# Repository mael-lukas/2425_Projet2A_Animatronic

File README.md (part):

<h1 align="center"> DEA : Dynamic Eagle Animatronic</h1>

<p align="center">An english version of this README file can be found below the french one</p>

<h2 align="center">Préambule</h2>
Depuis la Grêce antique et le mythe du géant de bronze Talos, les hommes ont toujours cherchés à créer des automates avec les moyens à leur disposition. Les animatroniques sont l'achèvement actuel de ce désir. Ce sont des poupées mécaniques plus ou moins réalistes dont le fonctionnement interne fait intervenir autant la mécanique que l'électronique.
Elles sont, depuis plusieurs décennies, et encore aujourd'hui principalement utilisées dans le domaine du divertissement au travers des parcs d'attractions, des films et des séries.

Dans le cadre d'un projet de deuxième année à l'école d'ingénieur française ENSEA ( École Nationale Supérieure de l'Électronique et de ses Applications), nous allons continuer la création d'une animatronique d'aigle royal démarrée au second semestre de l'année dernière.

# Sommaire 
  * #### Équipe et détail des tâches
  * #### Électronique et CAO
  * #### Modélisation & Impression 3D
  * #### Mécanique
  * #### Informatique
  * #### Résultat final
  * #### Points d'amélioration
  * #### Conclusion

<table>
  <tr>
    <td></td>
    <td></td>
  </tr>
</table>

<h1 align="center">Équipe</h1>

Membres de l'équipe : 
* #### Vincent Fernandes
    * [Github](https://github.com/FernandesVincent)
    * [Linkedin](https://www.linkedin.com/in/vincent-fernandes-0981552a6/)
* #### Maël Lukas
    * [Github](https://github.com/mael-lukas)
    * [Linkedin](https://www.linkedin.com/in/mael-lukas/)
* ##### Romane Ponthieu
    * [Github](https://github.com/Romanepnth)
    * [Linkedin](https://www.linkedin.com/in/romane-ponthieu/)
* #### Sedrenn Labrousse
    * [Github](https://github.com/Sedrennl)
    * [Linkedin](https://www.linkedin.com/in/sédrenn-labrousse-24b2a5295/)

* #### Supervisé par Nicolas Papazoglou
    * [Github](https://github.com/DBXYD?tab=overview&from=2024-05-01&to=2024-05-29)
    * [Linkedin](https://www.linkedin.com/in/nicolas-papazoglou-38382646/?originalSubdomain=fr)
 
* #### Supervisé par Laurent Fiack
    * [Github](https://github.com/lfiack)
    * [Linkedin](https://fr.linkedin.com/in/laurent-fiack-1b1415124)

Nous vous invitons à consulter notre [github de l'année dernière](https://github.com/mael-lukas/2324_Projet1AB_Animatronic), dans lequel vous pourrez trouver toutes les bases sur lesquelles nous avons démarré ce projet.

Ce projet s'articule autour de plusieurs compétences techniques : informatique, électronique & CAO, modélisation & impression 3D et mécanique. Chacune ayant partagée entre différents membres de l'équipe.

   * Informatique

Cette partie a été majoritairement traitée par Maël avec également, de manière plus minoritaire, Vincent.
Dans cette partie nous allons voir comment tout le code nécessaire au bon fonctionnement du DEA se présente. En partant de simple envoies de PWM pour commander des servomoteurs à la programmation de moteurs plus complexes, en passant par l'allumage de LED neopxiel et de la communication Bluetooth.

   * Électronique & CAO

Cette partie concerne différentes sous compétences : la conception des PCB, la soudure de ceux-ci, les test associés et finalement le sertissage et cablâge. 
Comme notre projet inclus plusieurs PCBs, leur conception a été réalisée par Vincent (pour les PCBs du corps et du gant) et Romane (pour le PCB de la tête).
Les soudures CMS ont été réalisées par Maël et Romane, tandis que les soudures THT ont été effectuées par Vincent.
Le sertissage et le cablâge ont également été réalisé par Vincent.

   * Modélisation & Impression 3D

Cette partie a été essentiellement traitée par Sedrenn aidée de Romane et Vincent. L'objectif de celle-ci étant de modéliser et d'imprimer l'aigle en taille 1:1 ainsi que des caches pour protéger l'alimentation et les PCBs.

   * Mécanique

Cette partie concerne la gestion des différents moteurs qui a été faite par Maël pour l'implémentation du code, par Vincent pour le cablâge de ceux-ci et leur placement sur la structure de l'aigle mais également par Sedrenn et Romane pour la conception des pièces 3D permettant de faire les liaisons entre ceux-ci.

<h1 align="center">Électronique & CAO</h1>

Pour commencer, veuillez trouver ci-dessous le diagramme d'architecture qui nous a servis de base pour la création des PCB de ce projet:

<div align="center">
  
</div>

Voici donc, le schematic et le routage du PCB principal de projet, le PCB du corps :

<table>
  <tr>
    <td></td>
    <td></td>
  </tr>
</table>

Ce PCB a eu le droit à plusieurs versions afin de l'améliorer à chaque ittération. La dernière en date est l'ajout de R1, une résistance de pull-up pour le protocol UART qui nous sert à commander les moteurs. Cependant, une fois ce nouveau PCB soudé et testé nous n'arrivions plus à communiquer avec les moteurs donc nous sommes repassé sur la version antérieure du PCB, qui elle est foncitonnel, où la résistance de pull-up est activée sur STM32CubeIDE.
Vous pouvez trouvez [ici](https://github.com/mael-lukas/2425_Projet2A_Animatronic/blob/main/Hardware/pcb/Body/ProjetCorps.csv)la BOM de ce PCB.

Le second PCB que nous avons du réalisé est celui de la tête, vous constaterez qu'il n'a pas changé depuis [l'année dernière](https://github.com/mael-lukas/2324_Projet1AB_Animatronic) voici donc simplement son schematic, son routage et sa BOM :

<table>
  <tr>
    <td></td>
    <td></td>
  </tr>
</table>

[BOM](https://github.com/mael-lukas/2425_Projet2A_Animatronic/blob/main/Hardware/pcb/Head/bom%20t%C3%AAte)

Il est à noter qu'avec plus de temps nous aurions suremenent modifier ce PCB car les besoins de notre projet ont changés, nous n'avons plus besoin de contrôler six servomoteurs mais par contre nous avons besoin d'une piste GPIO pour contrôler l'état haut ou bas de la pin XSDN du [TOF](https://github.com/mael-lukas/2425_Projet2A_Animatronic/blob/main/Datasheets/vl53l1x-satel.pdf).

Le troisième et dernier PCB de projet est le PCB du gant qui se présente comme suit :

<table>
  <tr>
    <td></td>
    <td></td>
  </tr>
</table>

[BOM](https://github.com/mael-lukas/2425_Projet2A_Animatronic/blob/main/Hardware/pcb/Gant/PCB_Gant/PCB_Gant.csv)

L'objectif avec ce PCB est de pouvoir commander les mouvements de l'aigle avec les mouvements de nos doigts et ce sans liaison filaire mais avec une liaison bluetooth grâce au module [HC05](https://github.com/mael-lukas/2425_Projet2A_Animatronic/blob/main/Datasheets/HC-05%20Datasheet.pdf). Les empreintes de résistances en 1206 correspondent aux pads des [flex sensors](https://github.com/mael-lukas/2425_Projet2A_Animatronic/blob/main/Datasheets/Flex_Sensor_Datasheet_v2019a-3304101.pdf) qui sont des résistances variables qui nous permmettent grâce aux circuits visibles sur le schematic d'avoir une tension seuil à partir de laquelle on peut activer tel ou tel mouvement de l'aigle.
Pour pouvoir fonctionner via une liaison Bluetooth nous alimentons le PCB grâce à une batterie Li-ion 1S et grâce à un module servant de Boost pour pouvoir amener une tension de +5V au pcb.

Ce PCB pourrait avoir des versions plus évoluées notamment vis à vis des circuits des [flex sensors](https://github.com/mael-lukas/2425_Projet2A_Animatronic/blob/main/Datasheets/Flex_Sensor_Datasheet_v2019a-3304101.pdf) qui peuvent être largement améliorer afin de par exemple pouvoir changer la tension seuil désirée avec des potentiomètres à la place des résistances.

Ce PCB permet également le contrôle du volume du haut parleur grâce à l'encodeur rotatif présent dessus. Pour revenir rapidement sur cette partie "haut parleur", l'objectif est de pouvoir jouer des sons grâce à un haut parleur présents entre les pattes de l'aigle en fonction de la distance avec la personne en face de lui grâce au [TOF](https://github.com/mael-lukas/2425_Projet2A_Animatronic/blob/main/Datasheets/vl53l1x-satel.pdf).Par exemple, si je me trouve à un mètre de l'oiseau il me dira "Bonjour" par contre si je m'approche à dix centimètres de celui-ci il me dira "Recule".

Pour finir cette partie, vous pouvez voir ci-dessous quelques photos des PCB réaliés. Vous constaterez qu'ils sont chacun entourés d'un support fait en impression 3D. Ces supports ne sont pas nécessaire in fine mais ils permettent d'éviter les risques en empéchant les collisions malheureuses entre les PCB, ce qui pourrait amener des problèmes si cela se passe lorsqu'ils sont en fonctionnement.

<h1 align="center">Modélisation & Impression 3D</h1>

Maintenant que nous avons commencé à parler de modélisation 3D il est temps d'attaquer totalement cette partie. En effet, nous avons décidés d'imprimer l'aigle entièrement en 3D en le vidant bien sûr à l'intérieur afin de pouvoir y placer notre matériel. Nous avons séparés cette modélisation en 3 parties : la tête, les ailes et le reste.

## Tête
C'est sans aucun doute la partie la plus compliquée de cette modélisation car il faut la travailler pour faire en sorte que le bec et les paupières de l'aigle soit amovibles et contrôlables par des servomoteurs. Voici, ci-dessous le modèle 3D et l'impression de celle-ci.

<div align="center">
  
</div>

Le modèle 3D a été repris d'un modèle existant, puis il a du être modifié afin notamment de vider l'intérieur, pour permettre le placement des moteurs, mais aussi de rendre la bouche et les paupières ammovibles.

<table>
  <tr>
    <td></td>
    <td></td>
  </tr>
</table>

<table>
  <tr>
    <td></td>
    <td></td>
    <td></td>
  </tr>
</table>

## Ailes
À l'opposé de la tête, c'est la modééisation la plus simple de projet car elle consiste seulement en la réalisation de pièces permettant d'approximer les os de l'aigle avec des emplacements pour les moteurs de l'épaule et du coude. À cela il faut ajouter les modules rouges que vous pourrez voir ci-après qui permettent la pose des plumes.

<table>
  <tr>
    <td></td>
    <td></td>
    <td></td>
  </tr>
</table>

<table>
 <tr>
    <td></td>
    <td></td>
    <td></td>
 </tr>
</table>

## Corps
Au vu du temps disponible, nous avons juste eu le temps de travailler la cage toracique de l'oiseau et donc nous avons délaissé la queue et les pattes qui n'ont pas d'autres utilités à part apporter de l'esthétique au projet, là où l'abdomen possède, lui, un réel intérêt. En effet, il nous permet de ranger à l'intérieur l'ensemble de notre électronique et de notre câblage afin que le projet ne laisse, dans l'idéal, rien apparaître de l'extérieur si tenté un câble d'alimentation.

<table>
  <tr>
    <td></td>
    <td></td>
  </tr>
</table>

L'impression du corps à due se faire en quatres parties car nous avions une coontrainte de temps : les impressiosns ne peuvent pas durer plus de 12h et les dimensions des imprimantes 3D qui sont trop petites pour notre modélisation. En effet, les plus grandes imprimantes 3D que nous pssédons sont des Creality K1 Max qui permettent de réaliser des impressions en 300x300x300 or le corps de l'oiseau tend plutôt sur du 350x400x200. De plus, pour l'assemblage de ces quatres parties, au vu du temps mis à disposition pour ce projet nous n'avons pas pu prévoir de moyen d'emboîter et de désemboiter cette partie. Pour que le tout se tienne nous avons donc pris le partit de coller les différentes parties avec un pistolet à colle.

<h1 align="center">Mécanique</h1>

Nous avons rapidement abordé la question des moteurs dans la partie précédente mais pour l'aborder un peu plus en profondeur, nous utilisons deux références de moteurs pour ce projet, les [FS90](https://github.com/mael-lukas/2425_Projet2A_Animatronic/blob/main/Datasheets/FS90.pdf) et les [XL430](https://github.com/mael-lukas/2425_Projet2A_Animatronic/blob/main/Datasheets/XL430-W250-T.pdf). Les premiers sont des servomteur 180° permettant le choix d'une position sur un plage de 180° par l'envoi d'une PWM. Nous les utilisons pour commander le bec et les yeux de l'aigle car cela ne requiert que par de force. De l'autre côté, les XL430 nous servent pour les mouvement plus complexes et surtout qui demandent plus de force. En effet, nous utilisons six de ces moteurs pour réaliser les ailes de l'oiseau, sur chaque aile nous avons deux XL430 qui sont utilisés pour reproduire l'épaule et le troisième pour reproduire ce que nous pourrions appeler le coude. 

Vous l'avez peut-être remarquez sur les photos ci-dessus mais toutes les pièces liants les XL430 ont été réalisées en impression 3D à l'exceptio de la pièce liant les deux moteurs de l'épaule. En effet, nous avions également fait une première version de cette pièce en impression 3D mais le problème était qu'elle doit pouvoir soutenir tout le poids de l'aile. Cela a causé la destruction de la version 3D de la pièce lorsqu'i fallut tester les mouvements de l'aile. Pour pallier à cela nous avons commander la pièce en métal aurpès du fournisseur et c'est donc cette pièce que vous pouvez voir sur les photos ci-dessous:

<table>
  <tr>
    <td></td>
    <td></td>
  </tr>
</table>

<h1 align="center">Informatique</h1>

Cependant, tout cela ne pourrait pas fonctionner sans code. Voici, ci-dessous le diagramme d'architecture du code:

<div align="center">
  
</div>

Nous allons traiter chaque partie de code de gauche à droite d'après ce diagramme en commençant tout d'abord par le code pour la communication bluetooth entre le STM32G474RET6 et le STM32G431KBT6.

Il faut cependant noter que nous n'avons cependant pas eu le temps de le tester correctement.

Pour le code du TOF, cette partie a été particulièrement compliquée pour nous et avions finis par la laisser un peu de côté au profit d'autres parties mais finalement nous avons pu avoir accès à une librairie écrite par M. Fiack et disponible sur son github. En adaptant cette librairie au processeur que nous utilisons nous avons pu faire fonctionner le TOF correctement. 

Les XL4430 sont sans aucun doute la partie la plus complexe de tout le projet, même au bout de tant de temps à travailler dessus nous avons toujours des problèmes dont nous ne comprenons pas la présence. En particulier, lorsque l'exact même code fonctionnait une semaine auparavant.

Les LED neopixel sont quant à elles une partie assez simple que nous avions réussi à faire fonctionner par l'envoi de PWM avant de passer à une version plus avancée grâce à une librairie de M. Fiack qui utilise le DMA.

Finalement, le code du module est surement la partie qui nous a été le plus simple à réalisée et qui nous permet, avec le module suivant : https://www.gotronic.fr/art-module-mp3-uart-mp3player-38215.htm de pouvoir jouer n'importe quel son présent sur la carte micro SD.

<h1 align="center">Résultat final</h1>

Finalement à la fin de ce projet nous avons pu obtenir les résultats suivant :
* contrôle total des LED via DMA
* Audio fonctionnel (Haut parleur + module mp3)
* Moteurs XL430 et FS90 tous fonctionnels
* Modélisations et impressions finalisées
* PCB fonctionnels
* code fonctionnel

CI-dessous vous pouvez télécharger une vidéo avec l'actionnement des 6 moteurs XL430 ainsi que des photos du rendu final de l'aigle:

[Voir la vidéo](https://github.com/mael-lukas/2425_Projet2A_Animatronic/blob/main/Gestion%20de%20projet/moteurs%20fonctionnels.mp4)

<table>
  <tr>
    <td></td>
    <td></td>
  </tr>
</table>

<h1 align="center">Points d'amélioration</h1>

 Comme vous avez pu le voir le rendu des modélisations 3D n'est vraiment satisfaisant, ce qui devait être un aigle vacille visuellement entre un vautour et un aigle et un dindon.
 Il faudrait donc pour la suite de projet prévoir une refonte totale de l'apparence de l'oiseau quitte à même refaire une base et abandonner l'actuelle en métal.
 De plus, nous n'avons pas réussi à utiliser correctement le capteur de distance, en partie du au fait que le PCB sur lequel il doit être branché date du projet 2324 et qu'il   
 comporte un nombre d'erreurs assez importante. 
 De plus, le PCB du corps mériterait aussi quelques ajustement, notamment au niveau des valeurs et tailles des composants pour qu'ils s'adaptent à ceux que nous avons à l'école.
 Il faudrait également refaire une partie du câblage qui était manquante ou mal faîte à la fin du projet.
 À toutes ces améliorations s'en ajouteront d'autres qui en découlent.
 
<h1 align="center">Conclusion</h1>

Malgré le fait que ce projet n'a pas pu être complété au bout d'un an et demi de travail nous sommes conscient qu'il nous a permis à tous de nous améliorer de façon exponentielle dans chacun des aspects que ce projet à pu couvrir. Nous pensons donc continuer à travailler dessus afin de le finir dans une version bien meilleure version à compter de Septembre durant ce qui sera notre 3ème et dernière annèe à l'ENSEA.

************************************************************************************************************************************************************************************

<h1 align="center">ENGLISH VERSION</h1>

************************************************************************************************************************************************************************************

<h2 align="center">Preamble</h2>
Since ancient Greece and the myth of the bronze giant Talos, humans have always sought to create automatons with the means at their disposal. Animatronics are the current culmination of this desire. They are more or less realistic mechanical dolls whose internal functioning involves both mechanics and electronics.
For several decades, and still today, they are mainly used in the entertainment industry through theme parks, films, and series.

As part of a second-year project at the French engineering school ENSEA (École Nationale Supérieure de l'Électronique et de ses Applications), we will continue the creation of a golden eagle animatronic started in the second semester of last year.

# Table of Contents 
  * #### Team and Task Details
  * #### Electronics and CAD
  * #### 3D Modeling & Printing
  * #### Mechanics
  * #### Computer Science
  * #### Final Result
  * #### Points for Improvement
  * #### Conclusion

<table>
  <tr>
    <td></td>
    <td></td>
  </tr>
</table>

<h1 align="center">Team</h1>

Team members: 
* #### Vincent Fernandes
    * [Github](https://github.com/FernandesVincent)
    * [Linkedin](https://www.linkedin.com/in/vincent-fernandes-0981552a6/)
* #### Maël Lukas
    * [Github](https://github.com/mael-lukas)
    * [Linkedin](https://www.linkedin.com/in/mael-lukas/)
* ##### Romane Ponthieu
    * [Github](https://github.com/Romanepnth)
    * [Linkedin](https://www.linkedin.com/in/romane-ponthieu/)
* #### Sedrenn Labrousse
    * [Github](https://github.com/Sedrennl)
    * [Linkedin](https://www.linkedin.com/in/sédrenn-labrousse-24b2a5295/)

* #### Supervised by Nicolas Papazoglou
    * [Github](https://github.com/DBXYD?tab=overview&from=2024-05-01&to=2024-05-29)
    * [Linkedin](https://www.linkedin.com/in/nicolas-papazoglou-38382646/?originalSubdomain=fr)
 
* #### Supervised by Laurent Fiack
    * [Github](https://github.com/lfiack)
    * [Linkedin](https://fr.linkedin.com/in/laurent-fiack-1b1415124)

We invite you to consult our [GitHub from last year](https://github.com/mael-lukas/2324_Projet1AB_Animatronic), where you can find all the foundations on which we based this project.

This project is built around several technical skills: computer science, electronics & CAD, 3D modeling & printing, and mechanics. Each area was divided among different team members.

   * Computer Science

This part was mainly handled by Maël, with some minor contributions from Vincent.
In this section, we will see how all the code necessary for the proper functioning of the DEA is organized. Starting from simple PWM signals to control servomotors, to programming more complex motors, and including the control of neopixel LEDs and Bluetooth communication.

   * Electronics & CAD

This part concerns different sub-skills: PCB design, soldering, associated testing, and finally crimping and cabling.
As our project includes several PCBs, their design was carried out by Vincent (for the body and glove PCBs) and Romane (for the head PCB).
The SMD soldering was done by Maël and Romane, while the THT soldering was carried out by Vincent.
Crimping and cabling were also performed by Vincent.

   * 3D Modeling & Printing

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
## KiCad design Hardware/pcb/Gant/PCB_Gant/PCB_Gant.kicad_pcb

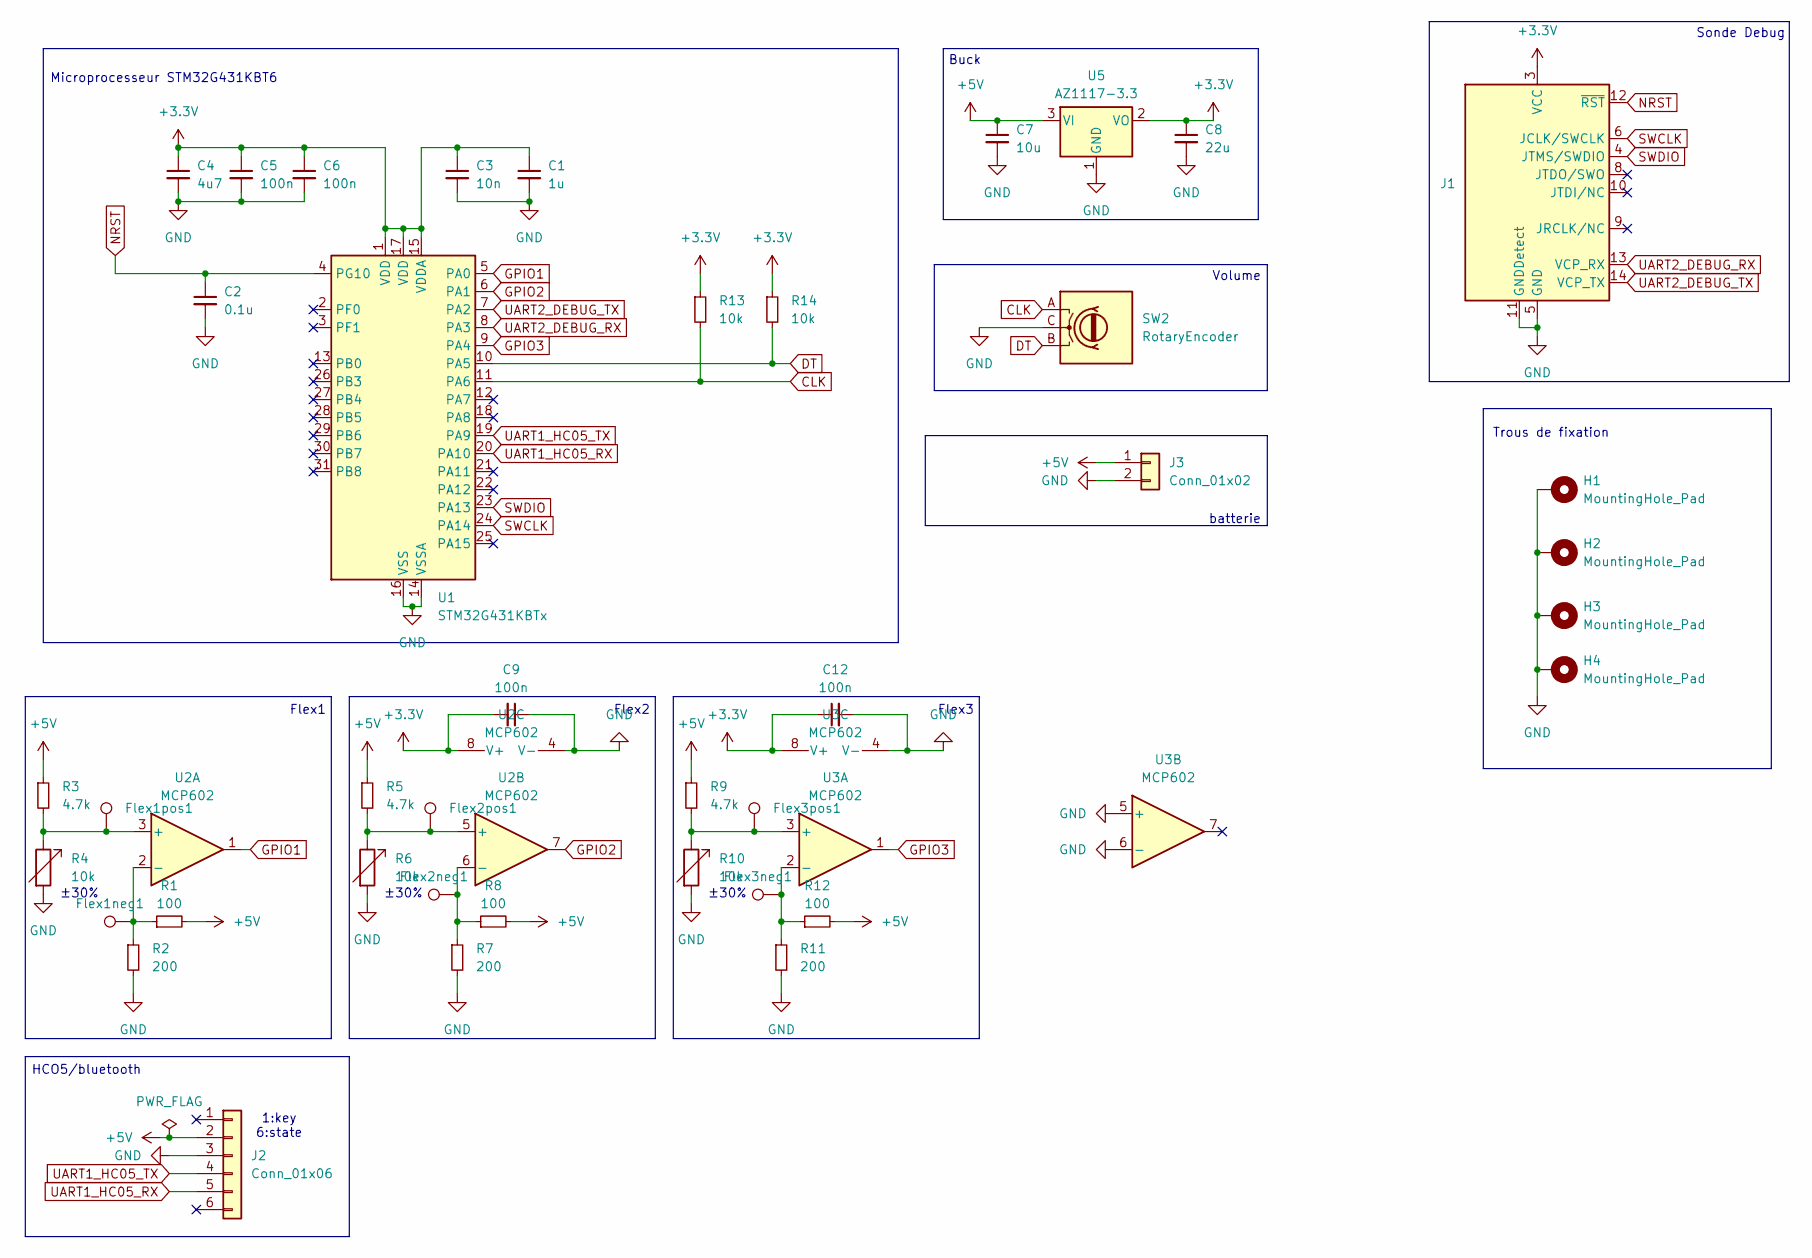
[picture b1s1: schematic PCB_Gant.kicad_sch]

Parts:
C1: 1u; C_0402_1005Metric
C2: 0.1u; C_0402_1005Metric
C3: 10n; C_0402_1005Metric
C4: 4u7; C_0402_1005Metric
C5, C6, C9, C12: 100n; C_0402_1005Metric
C7: 10u; C_0402_1005Metric
C8: 22u; C_Elec_5x5.4
Flex1neg1, Flex1pos1, Flex2neg1, Flex2pos1, Flex3neg1, Flex3pos1: TestPoint; TestPoint_Pad_D1.5mm
H1, H2, H3, H4: MountingHole_Pad; MountingHole_3.2mm_M3_Pad_Via
J1: Conn_ST_STDC14; PinHeader_2x07_P1.27mm_Vertical_SMD
J2: Conn_01x06; JST_EH_B6B-EH-A_1x06_P2.50mm_Vertical
J3: Conn_01x02; JST_EH_B2B-EH-A_1x02_P2.50mm_Vertical
R1, R8, R12: 100; R_0402_1005Metric
R2, R7, R11: 200; R_0402_1005Metric
R3, R5, R9: 4.7k; R_0402_1005Metric
R4, R6, R10: 10k; R_2512_6332Metric
R13, R14: 10k; R_0402_1005Metric
SW2: RotaryEncoder; RotaryEncoder_Alps_EC12E_Vertical_H20mm
U1: STM32G431KBTx; LQFP-32_7x7mm_P0.8mm
U2, U3: MCP602; SOIC-8_3.9x4.9mm_P1.27mm
U5: AZ1117-3.3; SOT-223-3_TabPin2; MPN AZ1117CH2-3.3TRG1

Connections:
+3.3V: C1.1, C3.1, C4.1, C5.1, C6.1, C8.1, C9.2, C12.1, J1.3 (VCC), R13.1, R14.1, U1.1 (VDD), U1.15 (VDDA), U1.17 (VDD), U2.8 (V+), U3.8 (V+), U5.2 (VO)
+5V: C7.1, J2.2, J3.1, R1.2, R3.1, R5.1, R8.2, R9.1, R12.2, U5.3 (VI)
CLK: R13.2, SW2.A, U1.11 (PA6)
DT: R14.2, SW2.B, U1.10 (PA5)
GND: C1.2, C2.2, C3.2, C4.2, C5.2, C6.2, C7.2, C8.2, C9.1, C12.2, H1.1, H2.1, H3.1, H4.1, J1.5 (GND), J1.7 (GND), J1.11 (GNDDetect), J2.3, J3.2, R2.2, R4.2, R6.2, R7.2, R10.2, R11.2, SW2.C, U1.14 (VSSA), U1.16 (VSS), U1.32 (VSS), U2.4 (V-), U3.4 (V-), U3.5 (+), U3.6 (-), U5.1 (GND)
GPIO1: U1.5 (PA0), U2.1
GPIO2: U1.6 (PA1), U2.7
GPIO3: U1.9 (PA4), U3.1
NRST: C2.1, J1.12 (~RST), U1.4 (PG10)
unnamed: Flex1pos1.1, R3.2, R4.1, U2.3 (+)
unnamed: Flex1neg1.1, R1.1, R2.1, U2.2 (-)
unnamed: Flex2pos1.1, R5.2, R6.1, U2.5 (+)
unnamed: Flex2neg1.1, R7.1, R8.1, U2.6 (-)
unnamed: Flex3pos1.1, R9.2, R10.1, U3.3 (+)
unnamed: Flex3neg1.1, R11.1, R12.1, U3.2 (-)
SWCLK: J1.6 (JCLK/SWCLK), U1.24 (PA14)
SWDIO: J1.4 (JTMS/SWDIO), U1.23 (PA13)
UART1_HC05_RX: J2.5, U1.20 (PA10)
UART1_HC05_TX: J2.4, U1.19 (PA9)
UART2_DEBUG_RX: J1.13 (VCP_RX), U1.8 (PA3)
UART2_DEBUG_TX: J1.14 (VCP_TX), U1.7 (PA2)

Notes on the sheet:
Volume
1:key 6:state
Trous de fixation
±30%
HCO5/bluetooth
Flex1
Microprocesseur STM32G431KBT6
Sonde Debug
Flex2
Buck
batterie
Flex3

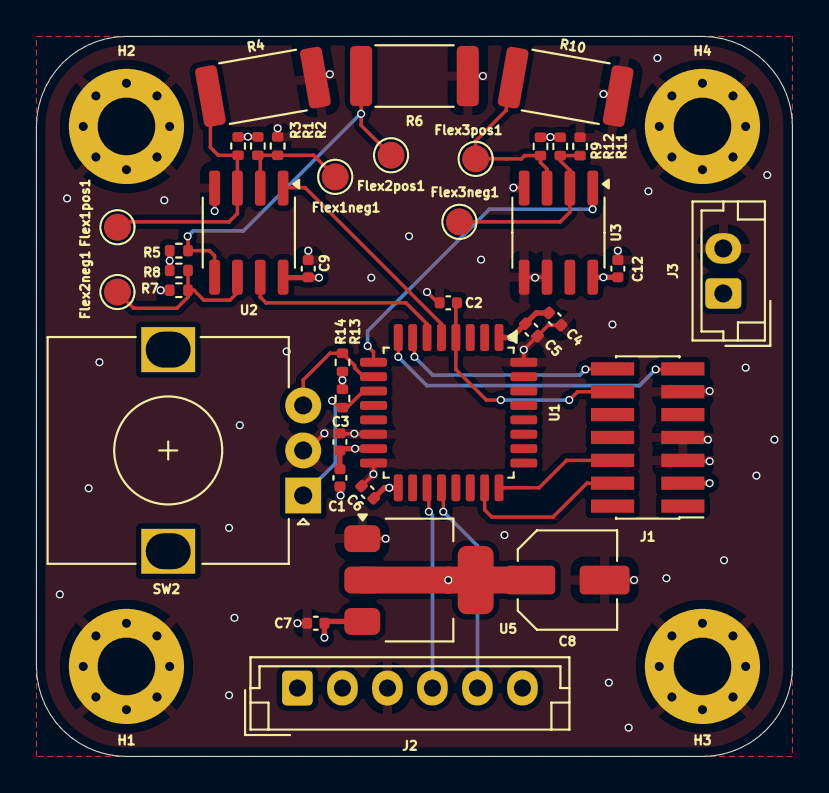
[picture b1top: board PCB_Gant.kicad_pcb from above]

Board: 4 copper layers, 42.0 x 40.0 mm, 42 parts (0 on the bottom side), 21 nets.

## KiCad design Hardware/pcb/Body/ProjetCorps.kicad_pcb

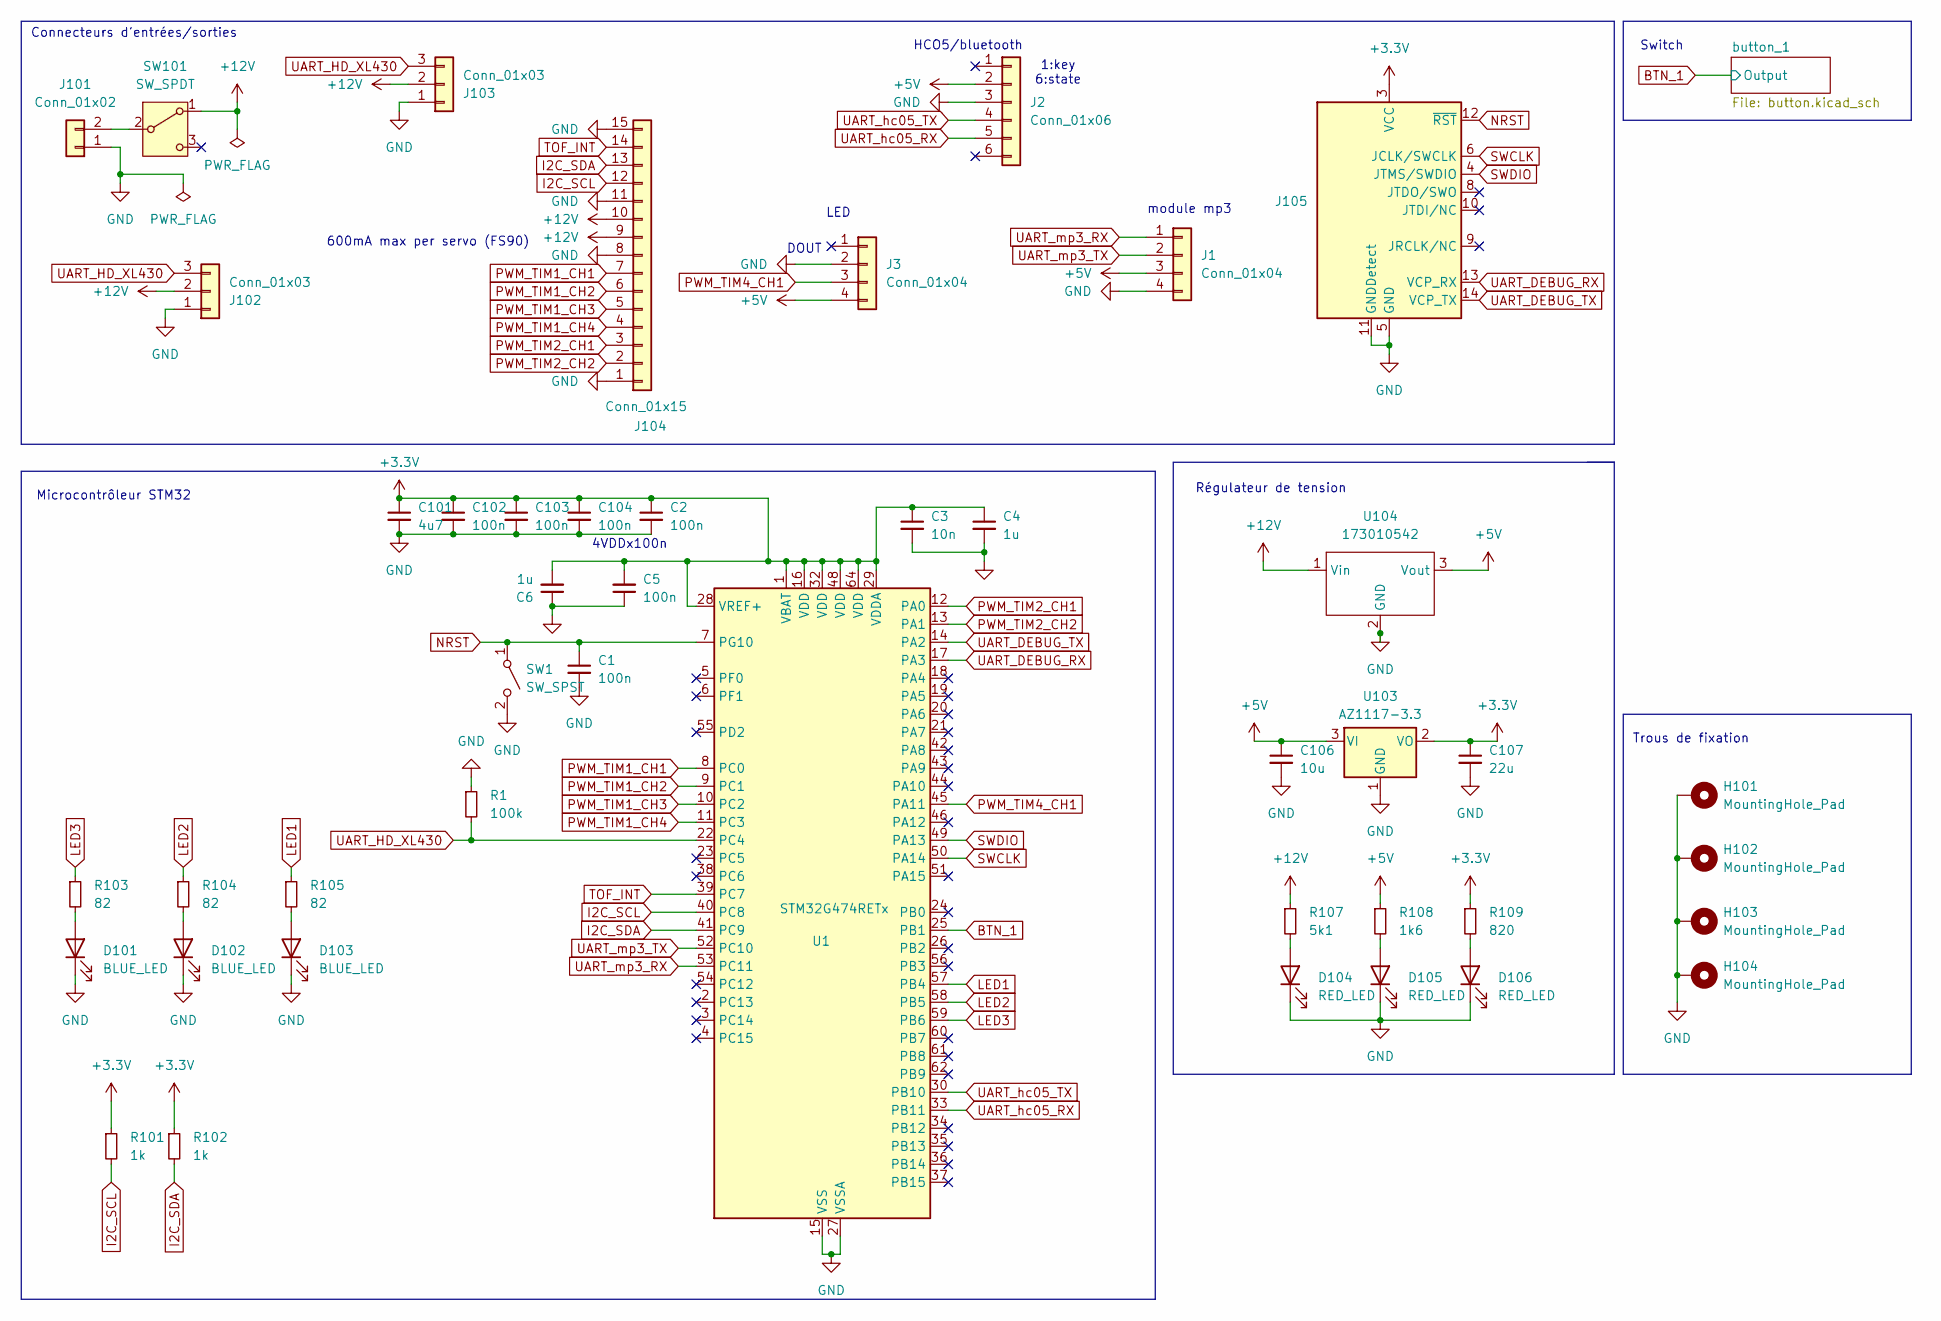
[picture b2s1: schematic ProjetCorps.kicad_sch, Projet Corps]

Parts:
C1, C2, C5, C102, C103, C104: 100n; C_0402_1005Metric
C3: 10n; C_0402_1005Metric
C4, C6: 1u; C_0402_1005Metric
C101: 4u7; C_0402_1005Metric
C106: 10u; C_0402_1005Metric
C107: 22u; C_Elec_5x5.4
D101, D102, D103: BLUE_LED; LED_0603_1608Metric; MPN 150060BS55040
D104, D105, D106: RED_LED; LED_0603_1608Metric; MPN 150060RS55040
H101, H102, H103, H104: MountingHole_Pad; MountingHole_3.2mm_M3_Pad_Via
J1, J3: Conn_01x04; JST_EH_B4B-EH-A_1x04_P2.50mm_Vertical
J2: Conn_01x06; JST_EH_B6B-EH-A_1x06_P2.50mm_Vertical
J101: Conn_01x02; AMASS_XT60-M_1x02_P7.20mm_Vertical
J102, J103: Conn_01x03; JST_EH_B3B-EH-A_1x03_P2.50mm_Vertical
J104: Conn_01x15; CONN15_31321_WRE; MPN 618015231421
J105: Conn_ST_STDC14; PinHeader_2x07_P1.27mm_Vertical_SMD
R1: 100k; R_0805_2012Metric
R101, R102: 1k; R_0402_1005Metric
R103, R104, R105: 82; R_0402_1005Metric
R107: 5k1; R_0402_1005Metric
R108: 1k6; R_0402_1005Metric
R109: 820; R_0402_1005Metric
SW1: SW_SPST; SW_Push_1P1T_NO_6x6mm_H9.5mm
SW101: SW_SPDT; 472123010111; MPN 472123010111
U1: STM32G474RETx; LQFP-64_10x10mm_P0.5mm
U103: AZ1117-3.3; SOT-223-3_TabPin2; MPN AZ1117CH2-3.3TRG1
U104: 173010542

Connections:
+3.3V: C2.1, C3.1, C4.1, C5.2, C6.2, C101.1, C102.1, C103.1, C104.1, C107.1, J105.3 (VCC), R101.1, R102.1, R109.1, U1.1 (VBAT), U1.16 (VDD), U1.28 (VREF+), U1.29 (VDDA), U1.32 (VDD), U1.48 (VDD), U1.64 (VDD), U103.2 (VO); also elsewhere on the board
+5V: C106.1, J1.3, J2.2, J3.4, R108.1, U103.3 (VI), U104.3 (Vout)
+12V: J102.2, J103.2, J104.9, J104.10, R107.1, SW101.1 (A), U104.1 (Vin)
BTN_1: U1.25 (PB1); also elsewhere on the board
GND: C1.2, C2.2, C3.2, C4.2, C5.1, C6.1, C101.2, C102.2, C103.2, C104.2, C106.2, C107.2, D101.1 (K), D102.1 (K), D103.1 (K), D104.1 (K), D105.1 (K), D106.1 (K), H101.1, H102.1, H103.1, H104.1, J1.4, J2.3, J3.2, J101.1, J102.1, J103.1, J104.1, J104.8, J104.11, J104.15, J105.5 (GND), J105.7 (GND), J105.11 (GNDDetect), R1.1, SW1.2 (B), U1.15 (VSS), U1.27 (VSSA), U1.31 (VSS), U1.47 (VSS), U1.63 (VSS), U103.1 (GND), U104.2 (GND); also elsewhere on the board
I2C_SCL: J104.12, R101.2, U1.40 (PC8)
I2C_SDA: J104.13, R102.2, U1.41 (PC9)
LED1: R105.1, U1.57 (PB4)
LED2: R104.1, U1.58 (PB5)
LED3: R103.1, U1.59 (PB6)
NRST: C1.1, J105.12 (~RST), SW1.1 (A), U1.7 (PG10)
unnamed: D101.2 (A), R103.2
unnamed: D102.2 (A), R104.2
unnamed: D103.2 (A), R105.2
unnamed: D104.2 (A), R107.2
unnamed: D105.2 (A), R108.2
unnamed: D106.2 (A), R109.2
unnamed: J101.2, SW101.2 (B)
PWM_TIM1_CH1: J104.7, U1.8 (PC0)
PWM_TIM1_CH2: J104.6, U1.9 (PC1)
PWM_TIM1_CH3: J104.5, U1.10 (PC2)
PWM_TIM1_CH4: J104.4, U1.11 (PC3)
PWM_TIM2_CH1: J104.3, U1.12 (PA0)
PWM_TIM2_CH2: J104.2, U1.13 (PA1)
PWM_TIM4_CH1: J3.3, U1.45 (PA11)
SWCLK: J105.6 (JCLK/SWCLK), U1.50 (PA14)
SWDIO: J105.4 (JTMS/SWDIO), U1.49 (PA13)
TOF_INT: J104.14, U1.39 (PC7)
UART_DEBUG_RX: J105.13 (VCP_RX), U1.17 (PA3)
UART_DEBUG_TX: J105.14 (VCP_TX), U1.14 (PA2)
UART_HD_XL430: J102.3, J103.3, R1.2, U1.22 (PC4)
UART_hc05_RX: J2.5, U1.33 (PB11)
UART_hc05_TX: J2.4, U1.30 (PB10)
UART_mp3_RX: J1.1, U1.53 (PC11)
UART_mp3_TX: J1.2, U1.52 (PC10)

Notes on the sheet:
HCO5/bluetooth
600mA max per servo (FS90)
module mp3
Microcontrôleur STM32
Switch
Connecteurs d'entrées/sorties
Trous de fixation
1:key 6:state
LED
4VDDx100n
Régulateur de tension
DOUT

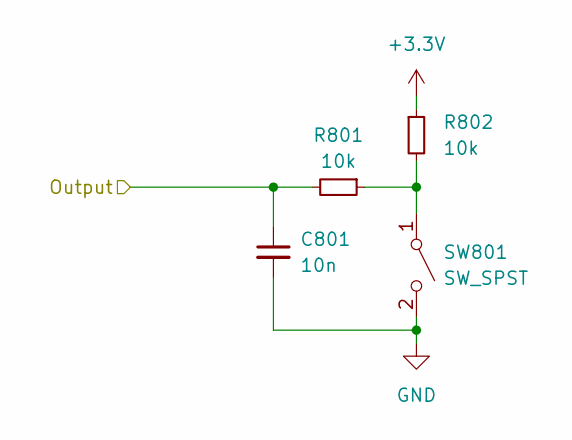
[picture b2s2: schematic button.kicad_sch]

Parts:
C801: 10n; C_0402_1005Metric
R801, R802: 10k; R_0402_1005Metric
SW801: SW_SPST; SW_Push_1P1T_NO_6x6mm_H9.5mm

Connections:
+3.3V: R802.1; also elsewhere on the board
BTN_1: C801.1, R801.2; also elsewhere on the board
GND: C801.2, SW801.2 (B); also elsewhere on the board
unnamed: R801.1, R802.2, SW801.1 (A)

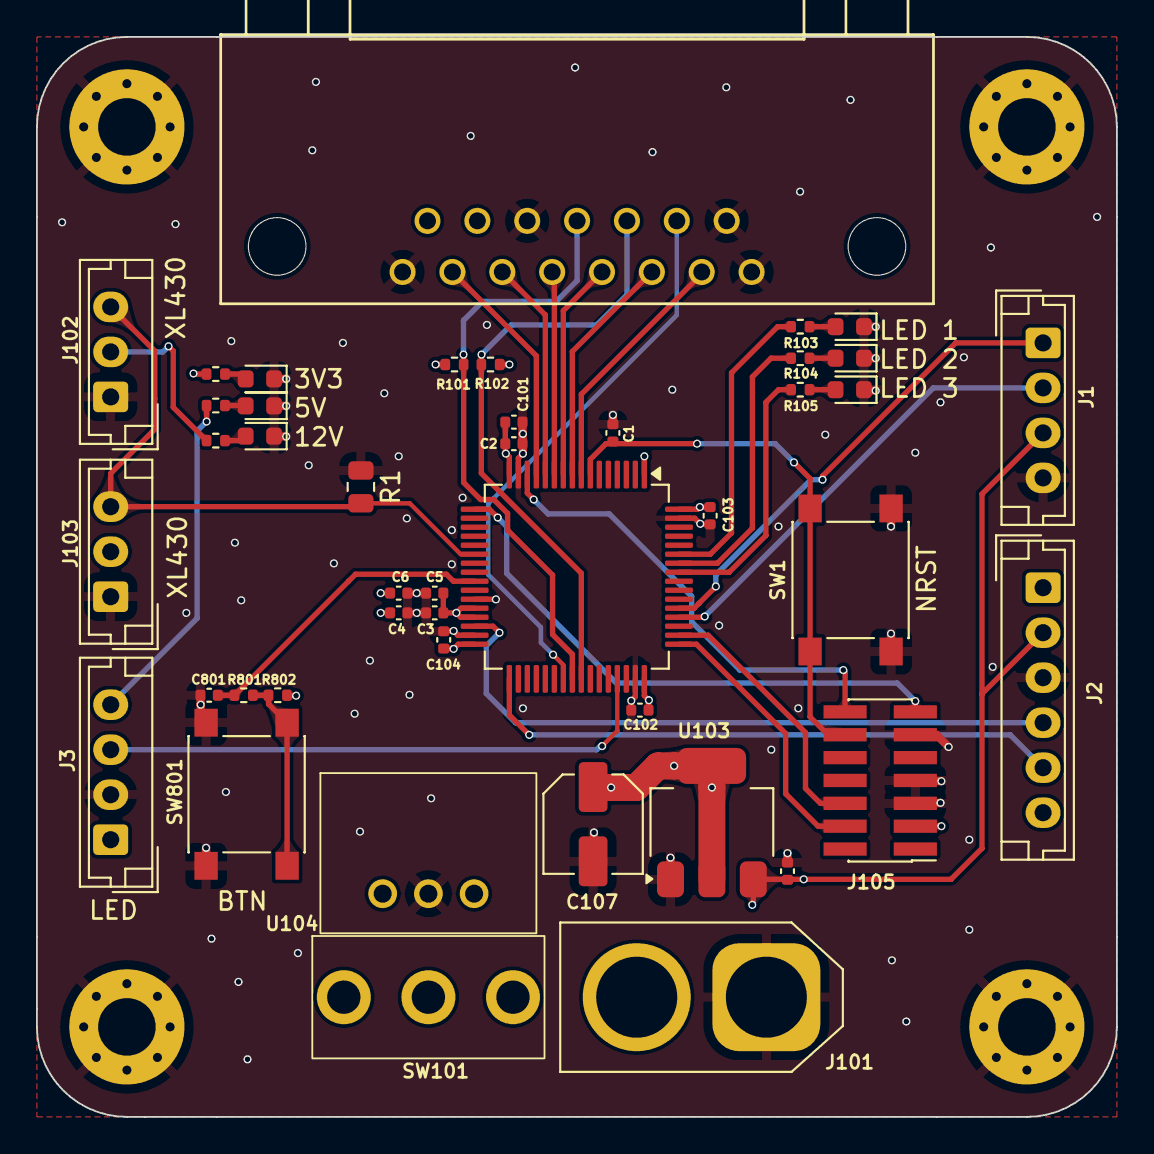
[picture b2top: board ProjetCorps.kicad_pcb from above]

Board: 4 copper layers, 60.0 x 60.0 mm, 48 parts (0 on the bottom side), 36 nets.

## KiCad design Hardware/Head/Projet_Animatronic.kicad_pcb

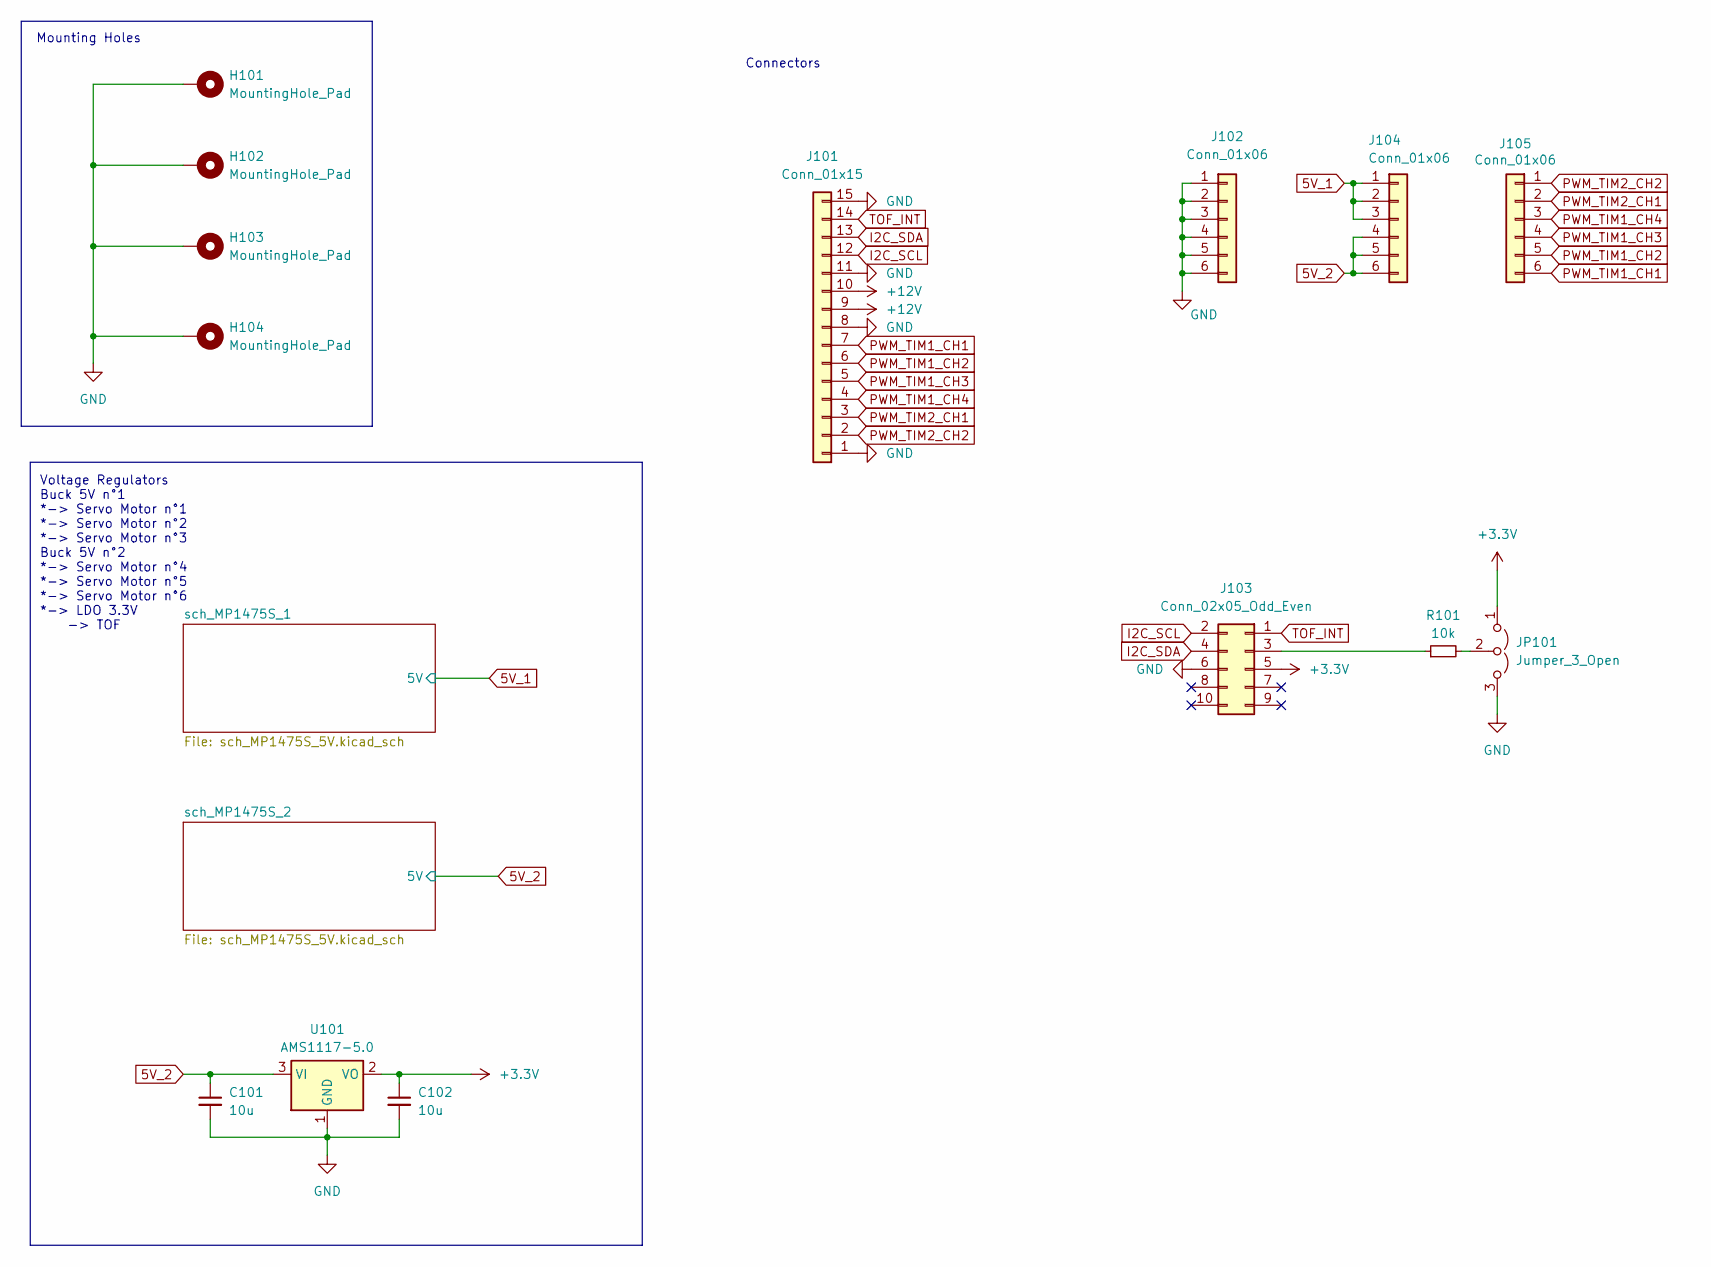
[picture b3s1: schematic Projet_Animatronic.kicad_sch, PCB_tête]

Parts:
C101, C102: 10u; C_0603_1608Metric
H101, H102, H103, H104: MountingHole_Pad; MountingHole_3.2mm_M3_Pad_Via
J101: Conn_01x15; CONN15_31321_WRE; MPN 618015231321
J102, J104, J105: Conn_01x06; PinHeader_1x06_P2.54mm_Vertical
J103: Conn_02x05_Odd_Even; PinHeader_2x05_P2.54mm_Vertical
JP101: Jumper_3_Open; SolderJumper-3_P1.3mm_Open_RoundedPad1.0x1.5mm_NumberLabels
R101: 10k; R_0603_1608Metric
U101: AMS1117-5.0; SOT-223-3_TabPin2

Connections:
5V_1: J104.1, J104.2, J104.3; also elsewhere on the board
5V_2: C101.1, J104.4, J104.5, J104.6, U101.3 (VI); also elsewhere on the board
+3.3V: C102.1, J103.5, JP101.1 (A), U101.2 (VO)
+12V: J101.9, J101.10; also elsewhere on the board
GND: C101.2, C102.2, H101.1, H102.1, H103.1, H104.1, J101.1, J101.8, J101.11, J101.15, J102.1, J102.2, J102.3, J102.4, J102.5, J102.6, J103.6, JP101.3 (B), U101.1 (GND); also elsewhere on the board
I2C_SCL: J101.12, J103.2
I2C_SDA: J101.13, J103.4
unnamed: J103.3, R101.1
unnamed: JP101.2 (C), R101.2
PWM_TIM1_CH1: J101.7, J105.6
PWM_TIM1_CH2: J101.6, J105.5
PWM_TIM1_CH3: J101.5, J105.4
PWM_TIM1_CH4: J101.4, J105.3
PWM_TIM2_CH1: J101.3, J105.2
PWM_TIM2_CH2: J101.2, J105.1
TOF_INT: J101.14, J103.1

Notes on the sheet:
Voltage Regulators Buck 5V n°1 *-> Servo Motor n°1 *-> Servo Motor n°2 *-> Servo Motor n°3 Buck 5V n°2 *-> Servo Motor n°4 *-> Servo Motor n°5 *-> Servo Motor n°6 *-> LDO 3.3V -> TOF
Connectors
Mounting Holes

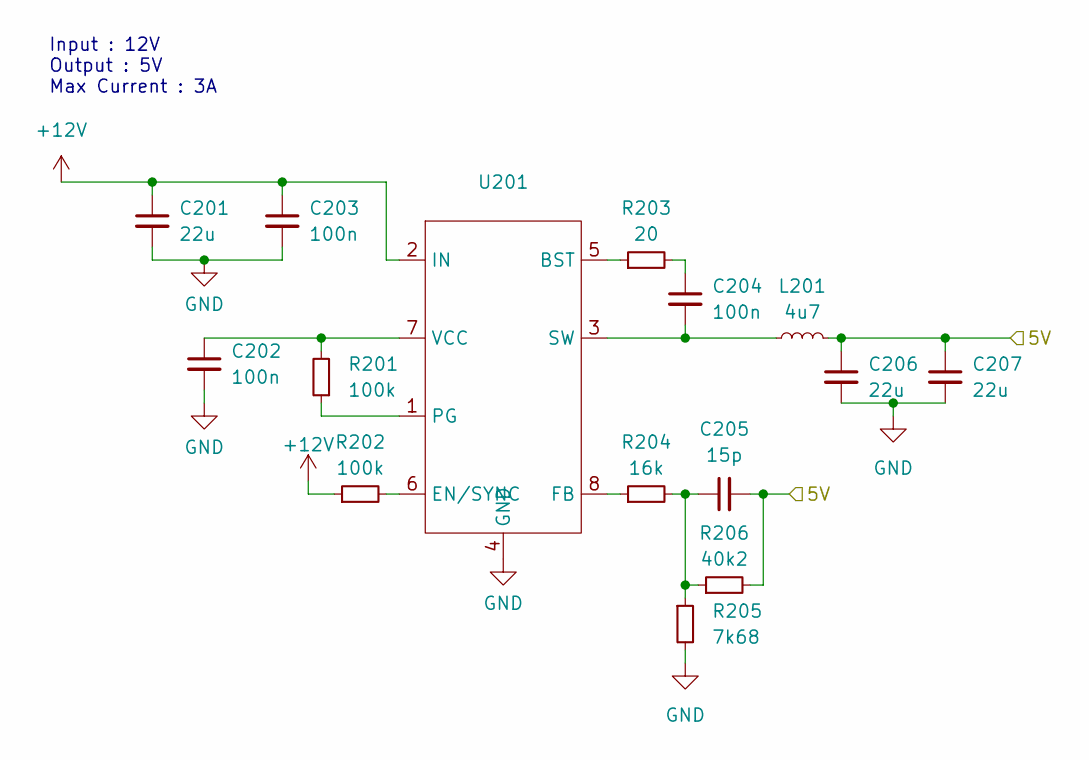
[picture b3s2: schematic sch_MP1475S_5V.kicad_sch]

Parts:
C201, C207: 22u; C_0805_2012Metric
C202, C203, C204: 100n; C_0603_1608Metric
C205: 15p; C_0603_1608Metric
C206: 22u; C_0603_1608Metric
L201: 4u7; 74404052047; MPN 74404052047
R201, R202: 100k; R_0603_1608Metric
R203: 20; R_0603_1608Metric
R204: 16k; R_0603_1608Metric
R205: 7k68; R_0603_1608Metric
R206: 40k2; R_0603_1608Metric
U201: TSOT-23-8

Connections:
5V_1: C205.2, C206.1, C207.1, L201.2, R206.2; also elsewhere on the board
+12V: C201.1, C203.1, R202.1, U201.2 (IN); also elsewhere on the board
GND: C201.2, C202.2, C203.2, C206.2, C207.2, R205.2, U201.4 (GND); also elsewhere on the board
unnamed: C204.1, R203.2
unnamed: C205.1, R204.2, R205.1, R206.1
unnamed: R203.1, U201.5 (BST)
unnamed: R202.2, U201.6 (EN/SYNC)
unnamed: R204.1, U201.8 (FB)
unnamed: R201.1, U201.1 (PG)
unnamed: C204.2, L201.1, U201.3 (SW)
unnamed: C202.1, R201.2, U201.7 (VCC)

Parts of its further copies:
C301, C307: 22u; C_0805_2012Metric
C302, C303, C304: 100n; C_0603_1608Metric
C305: 15p; C_0603_1608Metric
C306: 22u; C_0603_1608Metric
L301: 4u7; 74404052047; MPN 74404052047
R301, R302: 100k; R_0603_1608Metric
R303: 20; R_0603_1608Metric
R304: 16k; R_0603_1608Metric
R305: 7k68; R_0603_1608Metric
R306: 40k2; R_0603_1608Metric
U301: TSOT-23-8

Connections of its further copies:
5V_2: C305.2, C306.1, C307.1, L301.2, R306.2; also elsewhere on the board
+12V: C301.1, C303.1, R302.1, U301.2 (IN); also elsewhere on the board
GND: C301.2, C302.2, C303.2, C306.2, C307.2, R305.2, U301.4 (GND); also elsewhere on the board
unnamed: C304.1, R303.2
unnamed: C305.1, R304.2, R305.1, R306.1
unnamed: R303.1, U301.5 (BST)
unnamed: R302.2, U301.6 (EN/SYNC)
unnamed: R304.1, U301.8 (FB)
unnamed: R301.1, U301.1 (PG)
unnamed: C304.2, L301.1, U301.3 (SW)
unnamed: C302.1, R301.2, U301.7 (VCC)

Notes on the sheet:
Input : 12V Output : 5V Max Current : 3A

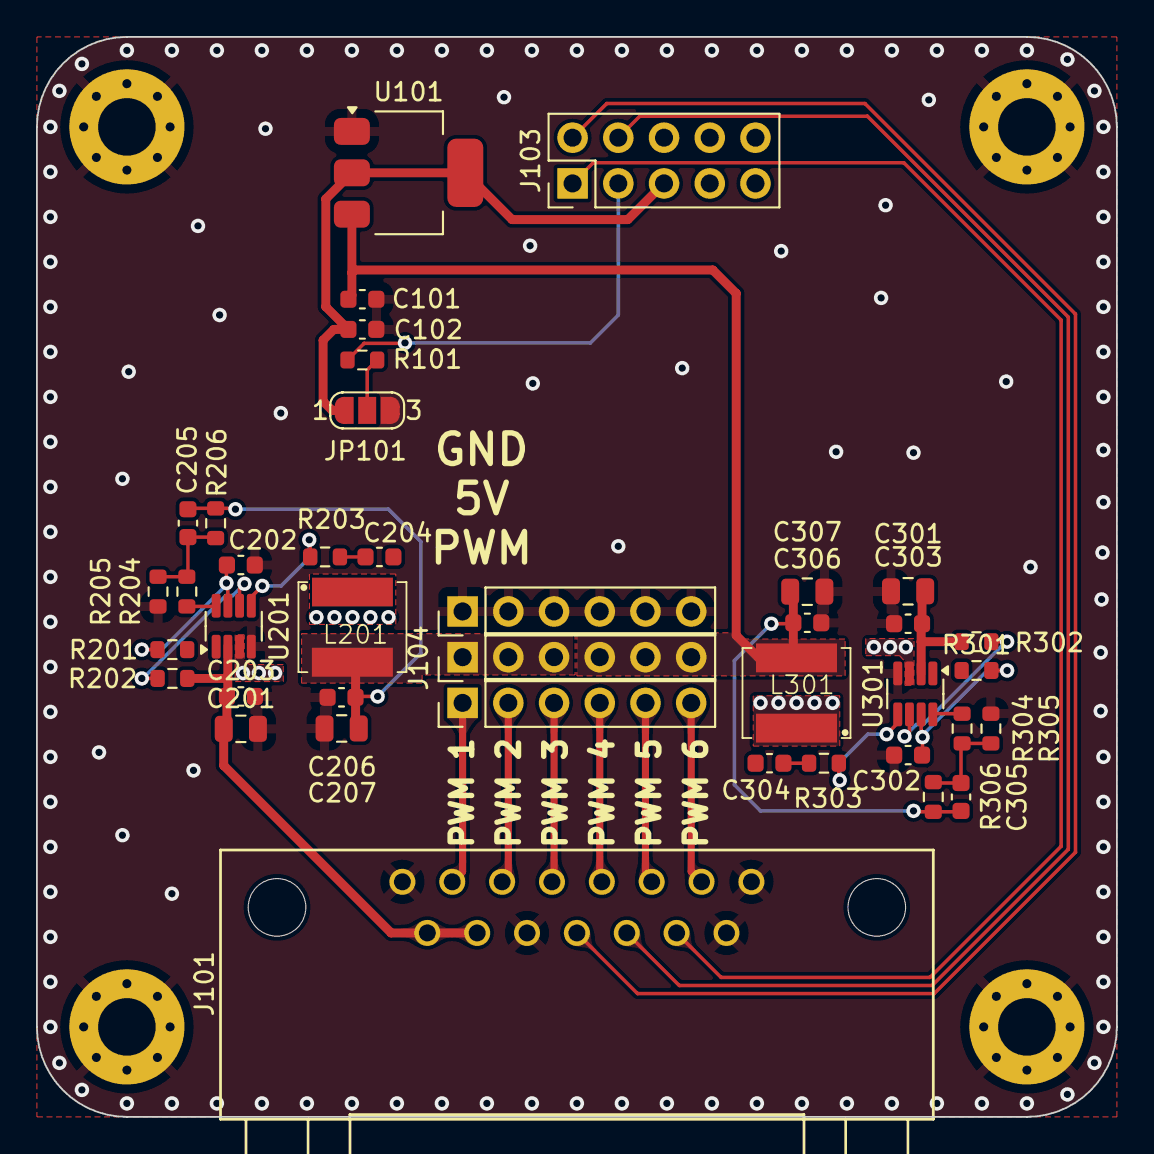
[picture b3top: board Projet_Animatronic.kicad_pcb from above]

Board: 2 copper layers, 60.0 x 60.0 mm, 44 parts (0 on the bottom side), 32 nets.

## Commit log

2024-09-17 Create files
2024-09-17 Imports de l'année dernière
2024-09-17 Imports année dernière
2024-09-24 Create jaaj
2024-10-01 nouveaux PCBs
2024-10-08 nouveau diagramme d'architecture
2024-10-08 diagramme archi.drawio
2024-10-08 tg.drawio
2024-10-08 led ds
2024-10-08 nouveau diagramme d'archi.drawio
2024-10-10 pinout L474RET6
2024-10-15 maj PCB
2024-10-22 update pcb body
2024-10-22 check Fiack
2024-10-22 update tof int
2024-10-22 gerber pcb body
2024-10-25 gerber pcb head
2024-11-05 Create ref
2024-11-05 Ajouté(e) archi_code.drawio
2024-11-05 Mettre à jour archi_code.drawio
2024-11-05 added archi_code in pdf format
2024-11-12 Create
2024-11-19 Create test
2024-12-03 TOF code
2024-12-03 S7 code for g474ret6
2024-12-10 architecture_code en png
2024-12-10 diagramme archi en png
2025-01-14 organized hardware
2025-01-14 fichiers stl
2025-01-21 added mp3 module driving via uart
2025-01-22 datasheets pour le gant
2025-01-24 pcb gant
2025-01-24 modifications on schematic
2025-01-25 PCB gant v1
2025-01-28 PCB gant V2
2025-01-28 Datasheet rotary encoder
2025-01-28 pcb body & gant maj
2025-01-28 meca_folder_organize
2025-01-28 PCB body & gant V3
2025-01-29 gerbers for body & gant
2025-02-24 added pseudo-protocol for bluetooth communication with strings
2025-02-24 Rename nouveau diagramme d'archi.pdf to diagramme_architecture.pdf
2025-02-24 Rename Untitled Diagram.drawio to diagramme_architecture.drawio
2025-02-24 Rename Screenshot from 2025-02-24 15-33-27.pdf to architecture_code.pdf
2025-02-24 Rename Screenshot from 2025-02-24 15-33-27.png to architecture_code.png
2025-02-24 Rename archi_code.drawio to architecture_code.drawio
2025-02-25 Mettre à jour diagramme_architecture.drawio
2025-02-25 updated diagramme_architecture
2025-02-25 Rename screenshot.pdf to diagramme_architecture.pdf
2025-02-25 Rename screenshot.png to diagramme_architecture.png
2025-04-01 V0 new readme
2025-04-01 probably the last commit ;(
2025-04-01 screens PCB
2025-04-01 rangement fichiers Stl
2025-04-01 update journal de bord
2025-04-01 datasheet TOF
2025-04-01 add HC05 datasheet
2025-04-01 add fichiers 3mf/stl
2025-04-01 maj tableau bord test
2025-04-22 Create pQf
